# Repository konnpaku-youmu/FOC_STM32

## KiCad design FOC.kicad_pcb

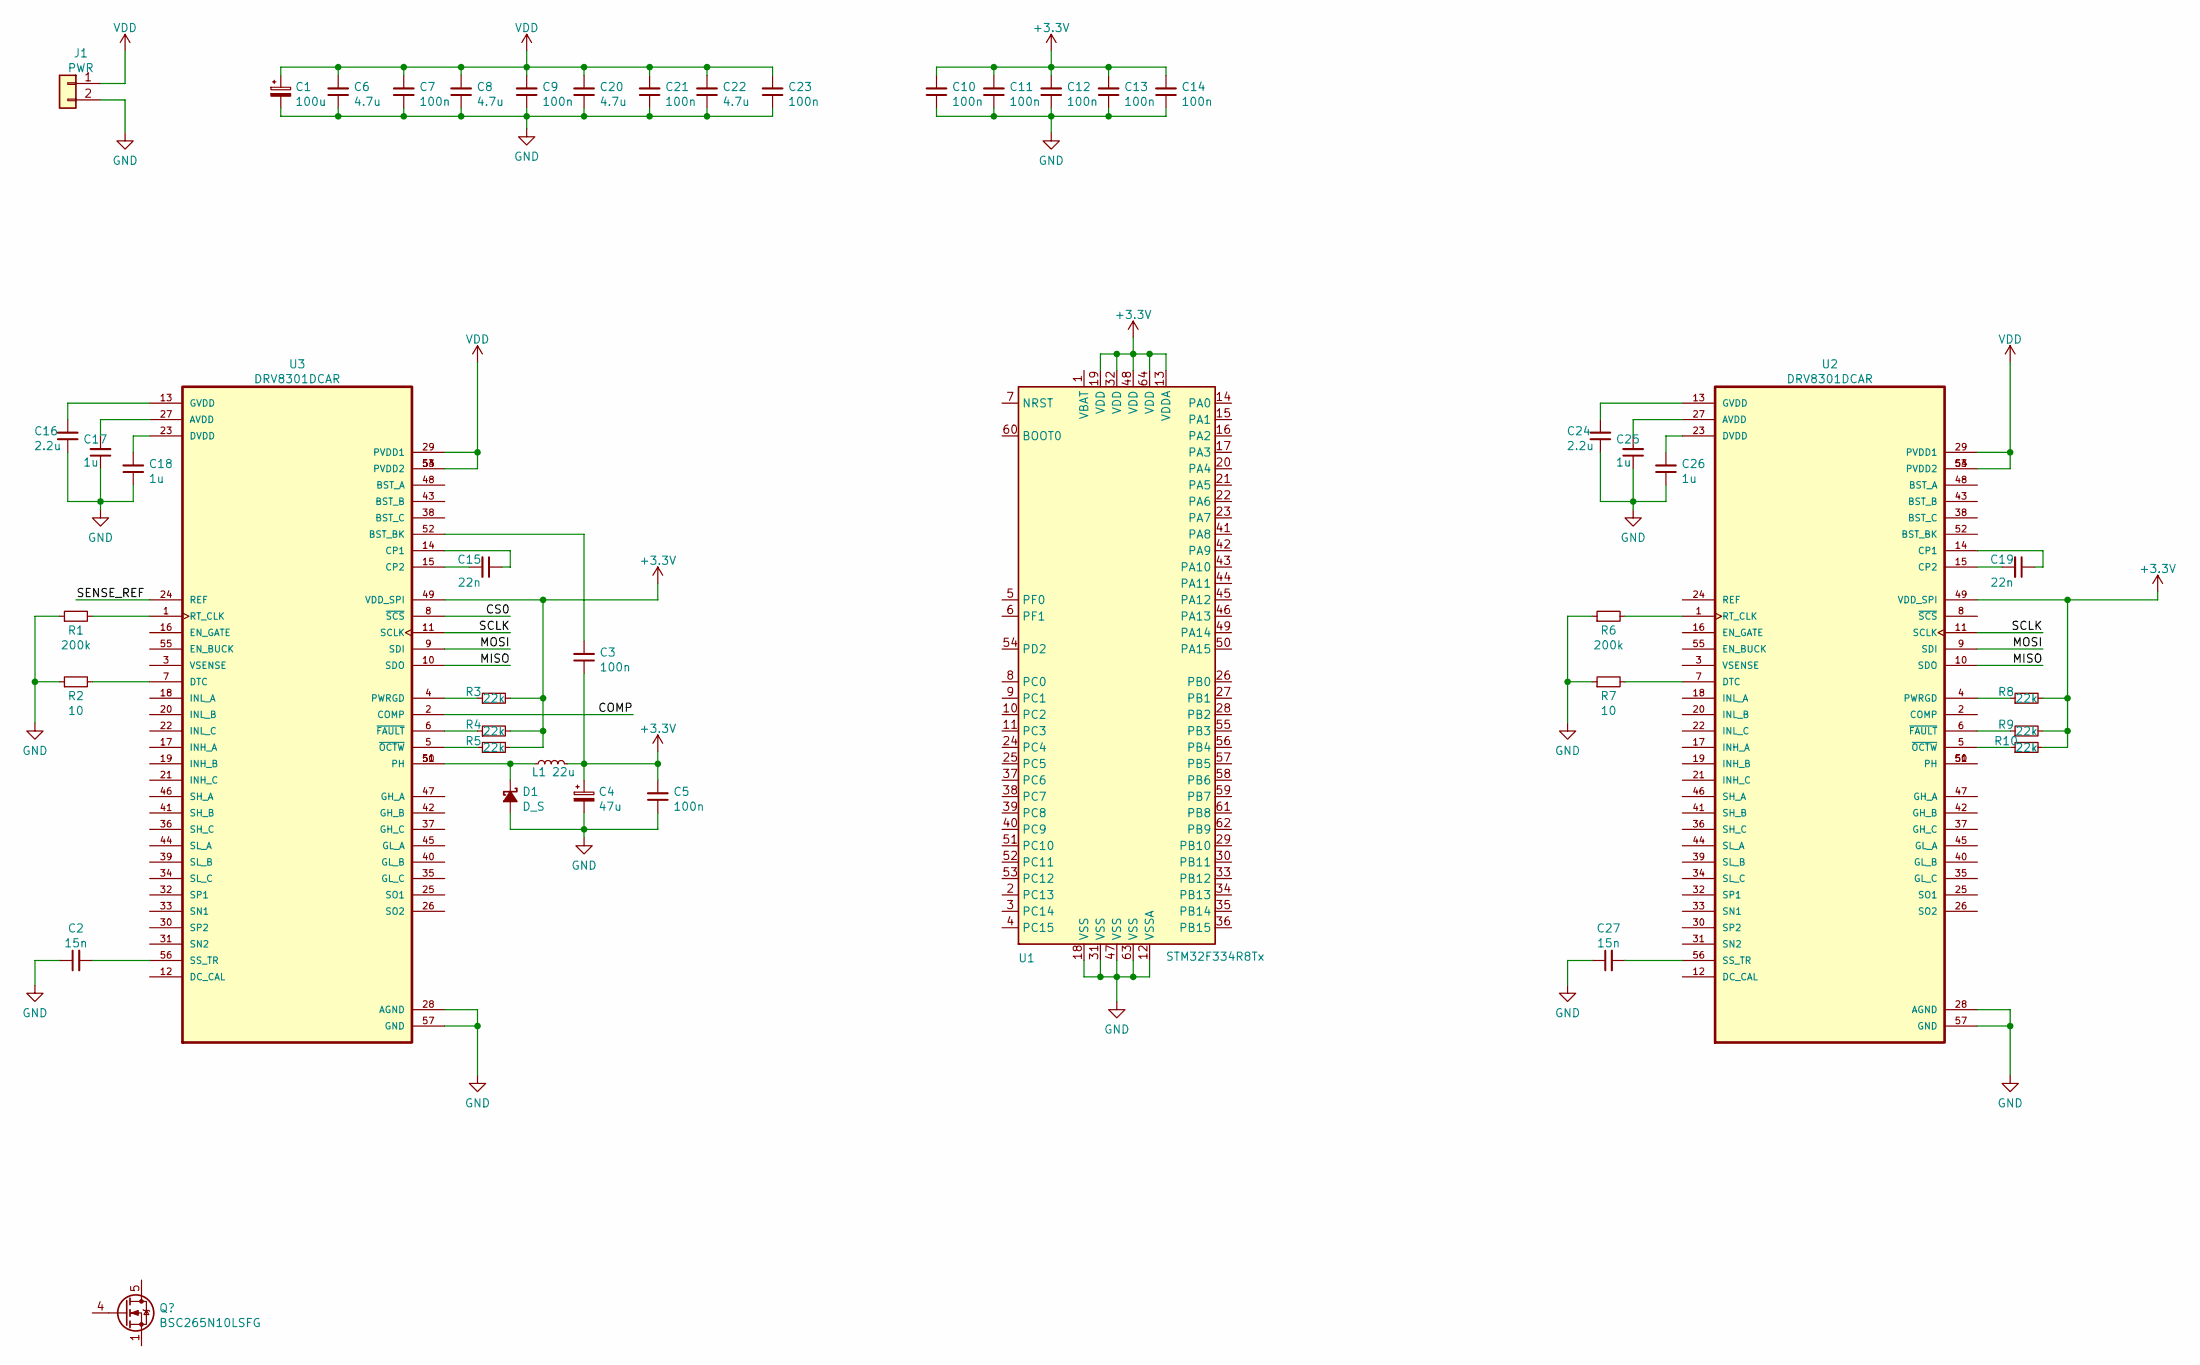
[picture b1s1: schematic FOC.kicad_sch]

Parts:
C1: 100u; CP_EIA-7343-30_AVX-N_Pad2.25x2.55mm_HandSolder
C2, C27: 15n; C_0603_1608Metric_Pad1.08x0.95mm_HandSolder
C3, C5, C7, C9, C10, C11, C12, C13, C14, C21, C23: 100n; C_0603_1608Metric_Pad1.08x0.95mm_HandSolder
C4: 47u; CP_EIA-7343-30_AVX-N_Pad2.25x2.55mm_HandSolder
C6, C8, C20, C22: 4.7u; C_0603_1608Metric_Pad1.08x0.95mm_HandSolder
C15, C19: 22n; C_0603_1608Metric_Pad1.08x0.95mm_HandSolder
C16, C24: 2.2u; C_0603_1608Metric_Pad1.08x0.95mm_HandSolder
C17, C18, C25, C26: 1u; C_0603_1608Metric_Pad1.08x0.95mm_HandSolder
D1: D_S; D_SOD-323_HandSoldering
J1: PWR; AMASS_XT60-M_1x02_P7.20mm_Vertical
L1: 22u; L_Sumida_CDMC6D28_7.25x6.5mm
R1, R6: 200k; R_0603_1608Metric_Pad0.98x0.95mm_HandSolder
R2, R7: 10; R_0603_1608Metric_Pad0.98x0.95mm_HandSolder
R3, R4, R5, R8, R9, R10: 22k; R_0603_1608Metric_Pad0.98x0.95mm_HandSolder
U1: STM32F334R8Tx; LQFP-64_10x10mm_P0.5mm
U2, U3: DRV8301DCAR; HTSSOP-56-1EP_6.1x14mm_P0.5mm_EP3.61x6.35mm; PARTREV F

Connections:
+3V3: C3.1, C4.1, C5.2, C10.2, C11.2, C12.2, C13.2, C14.2, L1.2, R3.2, R4.2, R5.2, R8.2, R9.2, R10.2, U1.13 (VDDA), U1.19 (VDD), U1.32 (VDD), U1.48 (VDD), U1.64 (VDD), U2.49 (VDD_SPI), U3.49 (VDD_SPI)
/COMP: U3.2 (COMP)
/CS0: U3.8 (~SCS)
/MISO: U2.10 (SDO), U3.10 (SDO)
/MOSI: U2.9 (SDI), U3.9 (SDI)
/SCLK: U2.11 (SCLK), U3.11 (SCLK)
/SENSE_REF: U3.24 (REF)
GND: C1.2, C2.1, C4.2, C5.1, C6.1, C7.1, C8.1, C9.1, C10.1, C11.1, C12.1, C13.1, C14.1, C16.1, C17.1, C18.1, C20.1, C21.1, C22.1, C23.1, C24.1, C25.1, C26.1, C27.1, D1.2 (A), J1.2, R1.1, R2.1, R6.1, R7.1, U1.12 (VSSA), U1.18 (VSS), U1.31 (VSS), U1.47 (VSS), U1.63 (VSS), U2.28 (AGND), U2.57 (GND), U3.28 (AGND), U3.57 (GND)
unnamed: C2.2, U3.56 (SS_TR)
unnamed: C3.2, U3.52 (BST_BK)
unnamed: C15.1, U3.14 (CP1)
unnamed: C15.2, U3.15 (CP2)
unnamed: C19.1, U2.14 (CP1)
unnamed: C19.2, U2.15 (CP2)
unnamed: C24.2, U2.13 (GVDD)
unnamed: C25.2, U2.27 (AVDD)
unnamed: C26.2, U2.23 (DVDD)
unnamed: D1.1 (K), L1.1, U3.50 (PH), U3.51 (PH)
unnamed: R1.2, U3.1 (RT_CLK)
unnamed: R2.2, U3.7 (DTC)
unnamed: R6.2, U2.1 (RT_CLK)
unnamed: R8.1, U2.4 (PWRGD)
unnamed: R10.1, U2.5 (~OCTW)
unnamed: R9.1, U2.6 (~FAULT)
unnamed: R7.2, U2.7 (DTC)
unnamed: U2.50 (PH), U2.51 (PH)
unnamed: C27.2, U2.56 (SS_TR)
unnamed: R3.1, U3.4 (PWRGD)
unnamed: R5.1, U3.5 (~OCTW)
unnamed: R4.1, U3.6 (~FAULT)
unnamed: C16.2, U3.13 (GVDD)
unnamed: C18.2, U3.23 (DVDD)
unnamed: C17.2, U3.27 (AVDD)
VDD: C1.1, C6.2, C7.2, C8.2, C9.2, C20.2, C21.2, C22.2, C23.2, J1.1, U2.29 (PVDD1), U2.53 (PVDD2), U2.54 (PVDD2), U3.29 (PVDD1), U3.53 (PVDD2), U3.54 (PVDD2)

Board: 2 copper layers, 49 parts (6 on the bottom side), 37 nets, no tracks yet.

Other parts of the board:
Q1, Q2, Q3, Q4, Q5, Q6: BSC061N08NS5; TDSON-8-1

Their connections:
unnamed: Q1.1 (S), Q1.2 (S), Q1.3 (S)
unnamed: Q2.1 (S), Q2.2 (S), Q2.3 (S)
unnamed: Q3.1 (S), Q3.2 (S), Q3.3 (S)
unnamed: Q4.1 (S), Q4.2 (S), Q4.3 (S)
unnamed: Q5.1 (S), Q5.2 (S), Q5.3 (S)
unnamed: Q6.1 (S), Q6.2 (S), Q6.3 (S)
